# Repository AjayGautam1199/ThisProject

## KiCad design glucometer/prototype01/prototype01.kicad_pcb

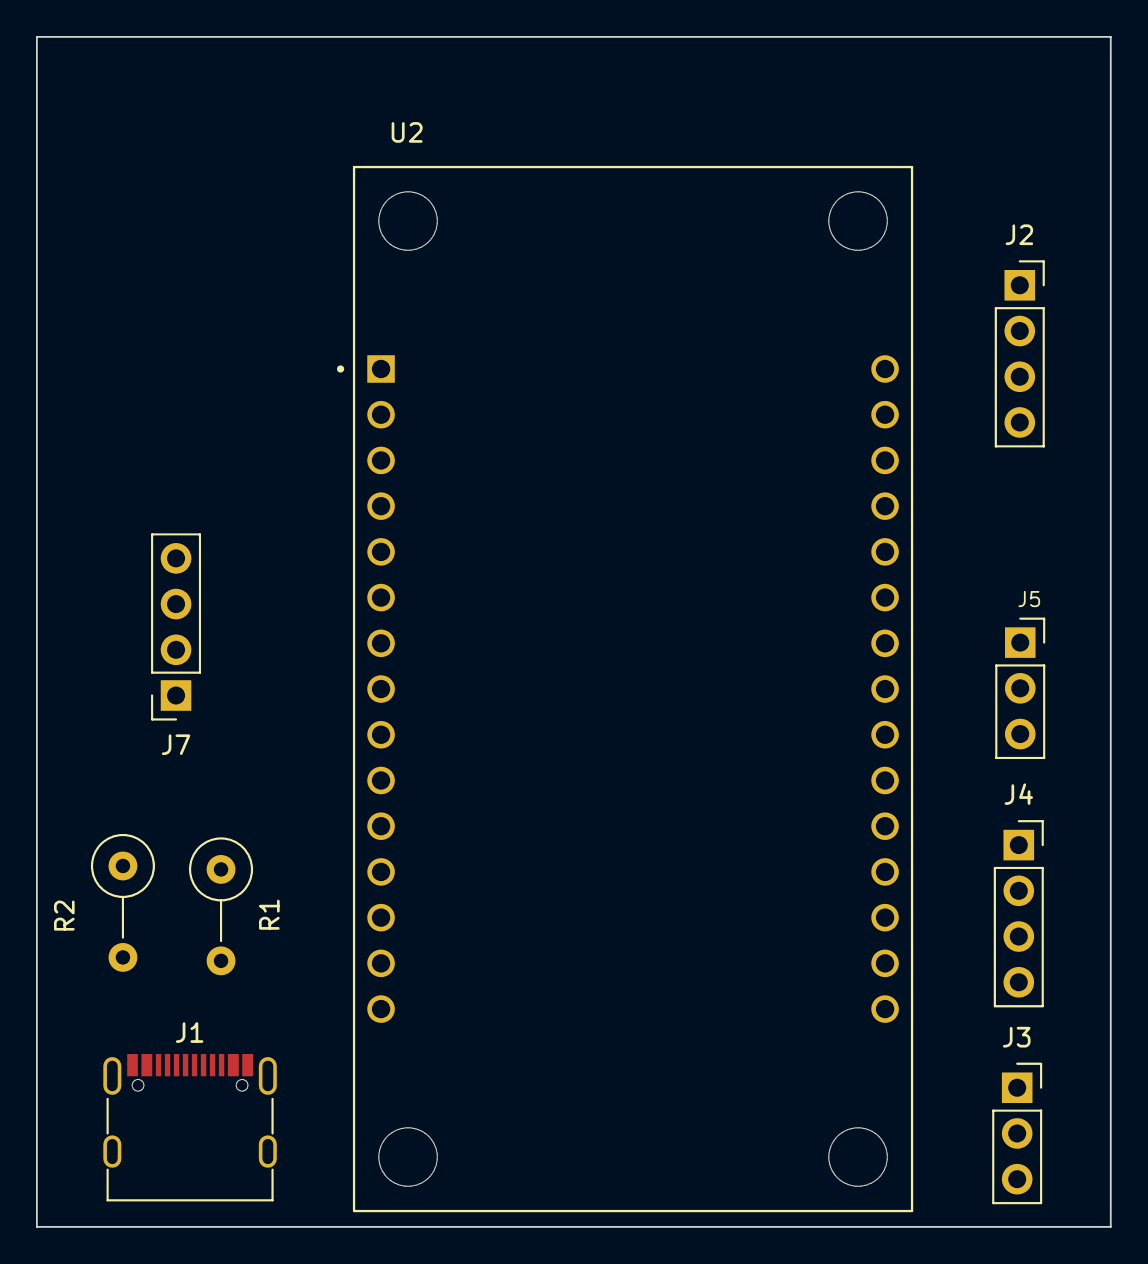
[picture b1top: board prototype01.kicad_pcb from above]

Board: 2 copper layers, 59.7 x 66.1 mm, 9 parts (0 on the bottom side), 15 nets, no tracks yet.

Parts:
J1: USB_C_USB2.0; USB_C_Receptacle_G-Switch_GT-USB-7010ASV
J2: OLED 128*64; PinSocket_1x04_P2.54mm_Vertical
J3: EYE BLINK; PinSocket_1x03_P2.54mm_Vertical
J4: IO PINS; PinSocket_1x04_P2.54mm_Vertical
J5: TEMPERATURE; PinSocket_1x03_P2.54mm_Vertical
J7: HEART RATE; PinSocket_1x04_P2.54mm_Vertical
R1, R2: 5K1; R_Axial_DIN0309_L9.0mm_D3.2mm_P5.08mm_Vertical
U2: ESP8266; MODULE_VMA107

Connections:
+5V: J1.A4 (VBUS), J1.A9 (VBUS), J1.B4 (VBUS), J1.B9 (VBUS), U2.15 (5V)
DATA A0: J7.3, U2.1 (A0)
GND: J1.A1 (GND), J1.A12 (GND), J1.B1 (GND), J1.B12 (GND), J1.S1 (SHIELD), J2.1, J3.2, J5.1, J7.2, R1.1, R2.1, U2.8 (GND), U2.10 (GND), U2.14 (GND), U2.17 (GND), U2.24 (GND)
IO1 D4: J5.3, U2.26 (D4)
IR D5: J3.1, U2.23 (D5)
unnamed: J1.A5 (CC1), R2.2
unnamed: J1.B5 (CC2), R1.2
unnamed: J4.1, U2.21 (D7)
unnamed: J4.2, U2.20 (D8)
unnamed: J4.3, U2.19 (D9)
unnamed: J4.4, U2.18 (D10)
POWER 3.3V: J3.3, J7.1, U2.9 (3V3), U2.11 (3V3), U2.16 (3V3), U2.25 (3V3)
SDA D2: J2.4, U2.28 (D2)
SDL D1: J2.3, U2.29 (D1)
TEMP D3: J5.2, U2.27 (D3)

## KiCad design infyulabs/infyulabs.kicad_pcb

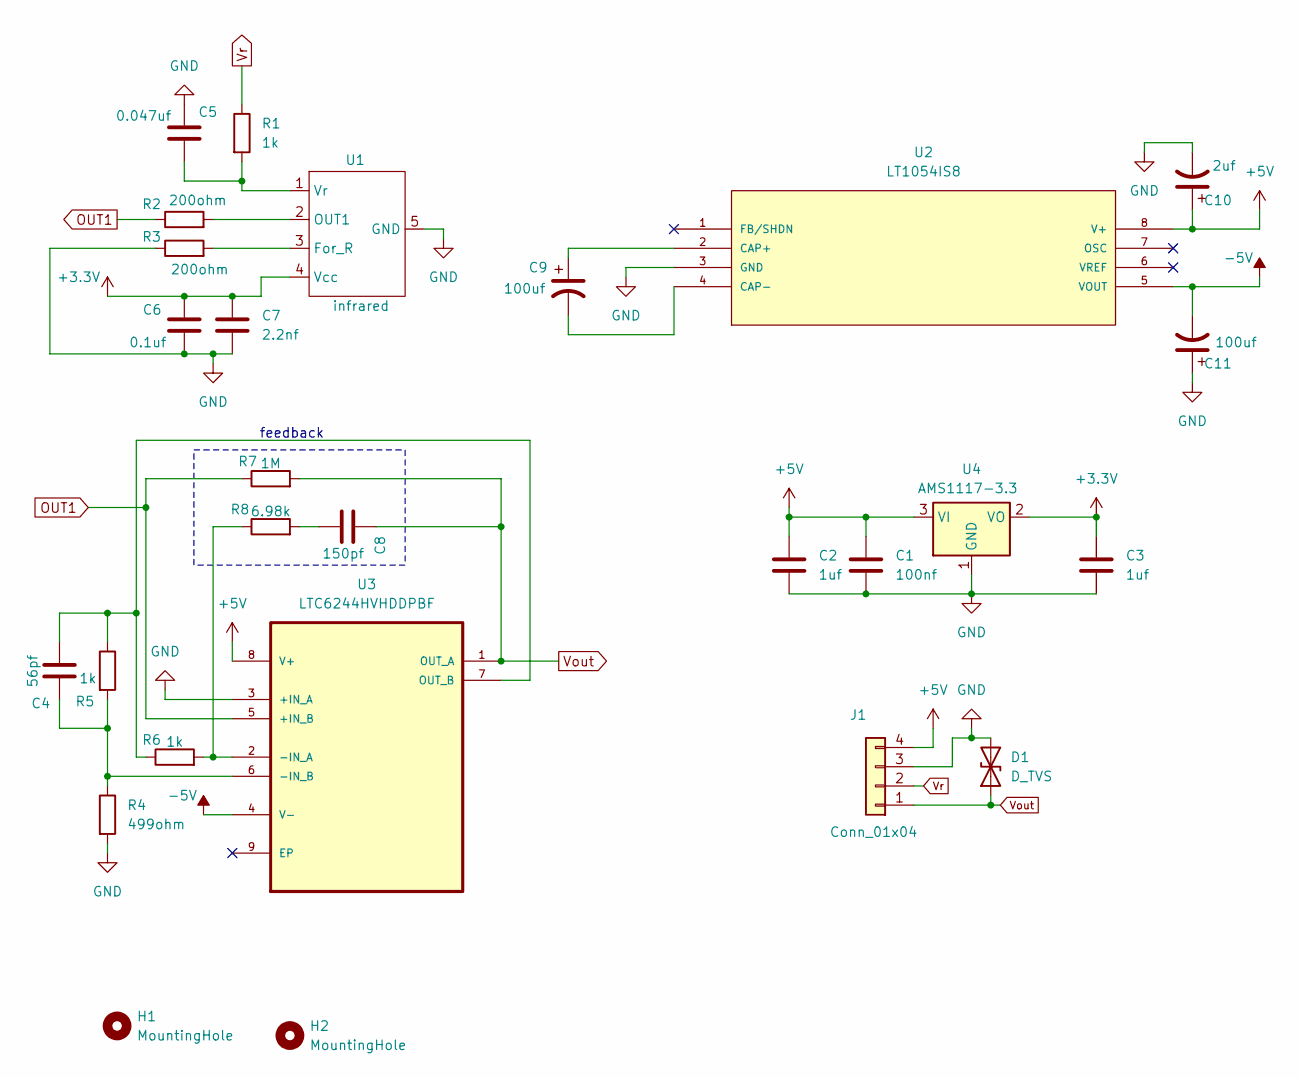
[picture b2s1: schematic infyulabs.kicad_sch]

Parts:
C1: 100nf; C_1206_3216Metric
C2, C3: 1uf; C_1206_3216Metric
C4: 56pf; C_1206_3216Metric
C5: 0.047uf; C_1206_3216Metric
C6: 0.1uf; C_1206_3216Metric
C7: 2.2nf; C_1206_3216Metric
C8: 150pf; C_1206_3216Metric
C9, C11: 100uf; C_1206_3216Metric
C10: 2uf; C_1206_3216Metric
D1: D_TVS; D_1210_3225Metric_Pad1.42x2.65mm_HandSolder
H1, H2: MountingHole; MountingHole_2.7mm_M2.5_Pad_Via
J1: Conn_01x04; JST_EH_B4B-EH-A_1x04_P2.50mm_Vertical
R1, R5, R6: 1k; R_1206_3216Metric
R2, R3: 200ohm; R_1206_3216Metric
R4: 499ohm; R_1206_3216Metric
R7: 1M; R_1206_3216Metric
R8: 6.98k; R_1206_3216Metric
U1: infrared; infrared_by_AG
U2: LT1054IS8; SO-8_S; MANUFACTURER_PART_NUMBER lt1054is8
U3: LTC6244HVHDDPBF; DFN300X300X80-9N; MPN LTC6244HVHDD#PBF
U4: AMS1117-3.3; SOT-223-3_TabPin2

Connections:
+3.3V: C3.1, C6.1, C7.1, U1.4 (Vcc), U4.2 (VO)
+5V: C1.1, C2.1, C10.1, J1.4, U2.8 (V+), U3.8 (V+), U4.3 (VI)
-5V: C11.2, U2.5 (VOUT), U3.4 (V-)
GND: C1.2, C2.2, C3.2, C5.1, C6.2, C7.2, C10.2, C11.1, D1.2 (A2), J1.3, R3.1, R4.2, U1.5 (GND), U2.3 (GND), U3.3 (+IN_A), U4.1 (GND)
unnamed: C8.1, R8.2
unnamed: R3.2, U1.3 (For_R)
unnamed: R2.2, U1.2 (OUT1)
unnamed: C5.2, R1.2, U1.1 (Vr)
unnamed: C9.1, U2.2 (CAP+)
unnamed: C9.2, U2.4 (CAP-)
unnamed: R6.2, R8.1, U3.2 (-IN_A)
unnamed: C4.2, R4.1, R5.2, U3.6 (-IN_B)
unnamed: C4.1, R5.1, R6.1, U3.7 (OUT_B)
OUT1: R2.1, R7.1, U3.5 (+IN_B)
Vout: C8.2, D1.1 (A1), J1.1, R7.2, U3.1 (OUT_A)
Vr: J1.2, R1.1

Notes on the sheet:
feedback

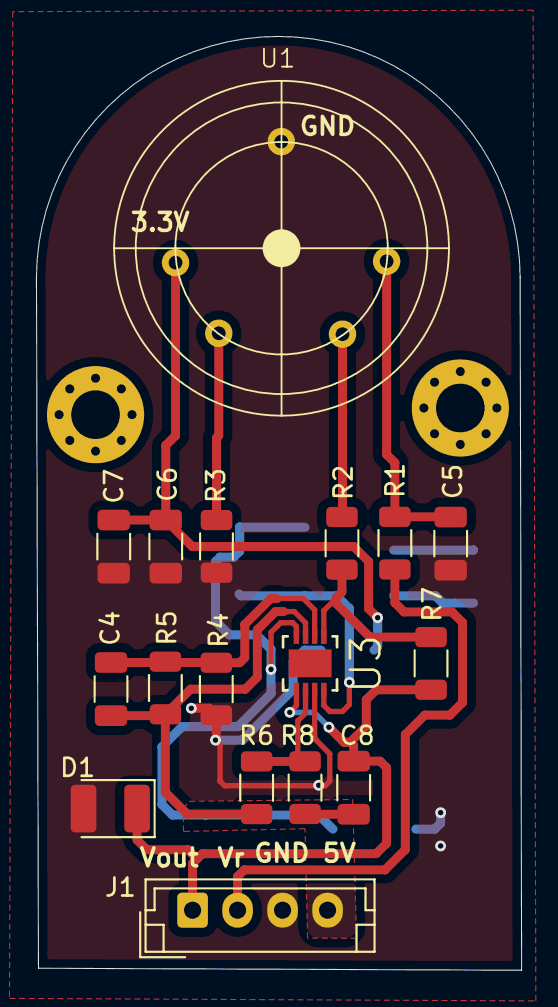
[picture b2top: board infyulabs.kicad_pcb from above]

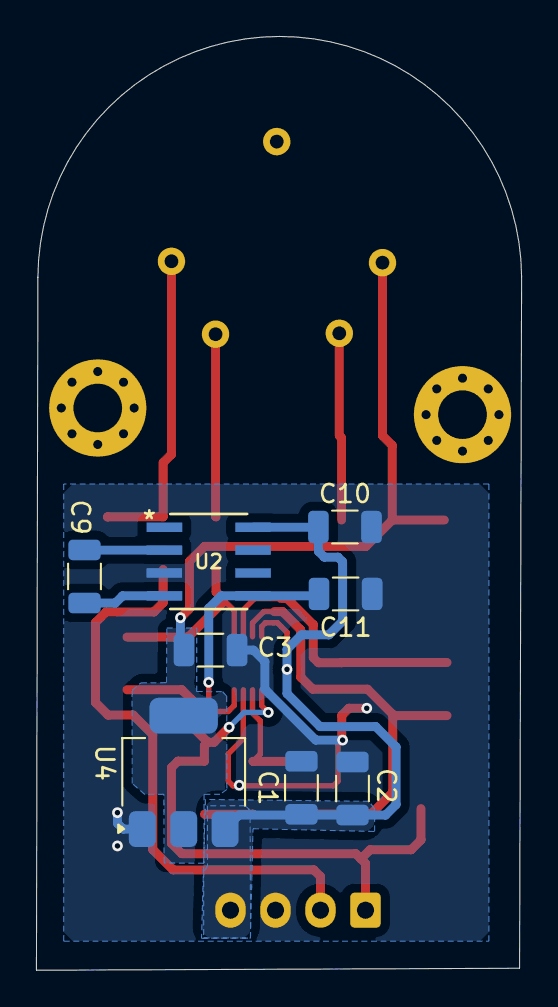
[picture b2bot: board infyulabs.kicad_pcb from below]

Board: 2 copper layers, 27.0 x 51.9 mm, 27 parts (8 on the bottom side), 16 nets.
